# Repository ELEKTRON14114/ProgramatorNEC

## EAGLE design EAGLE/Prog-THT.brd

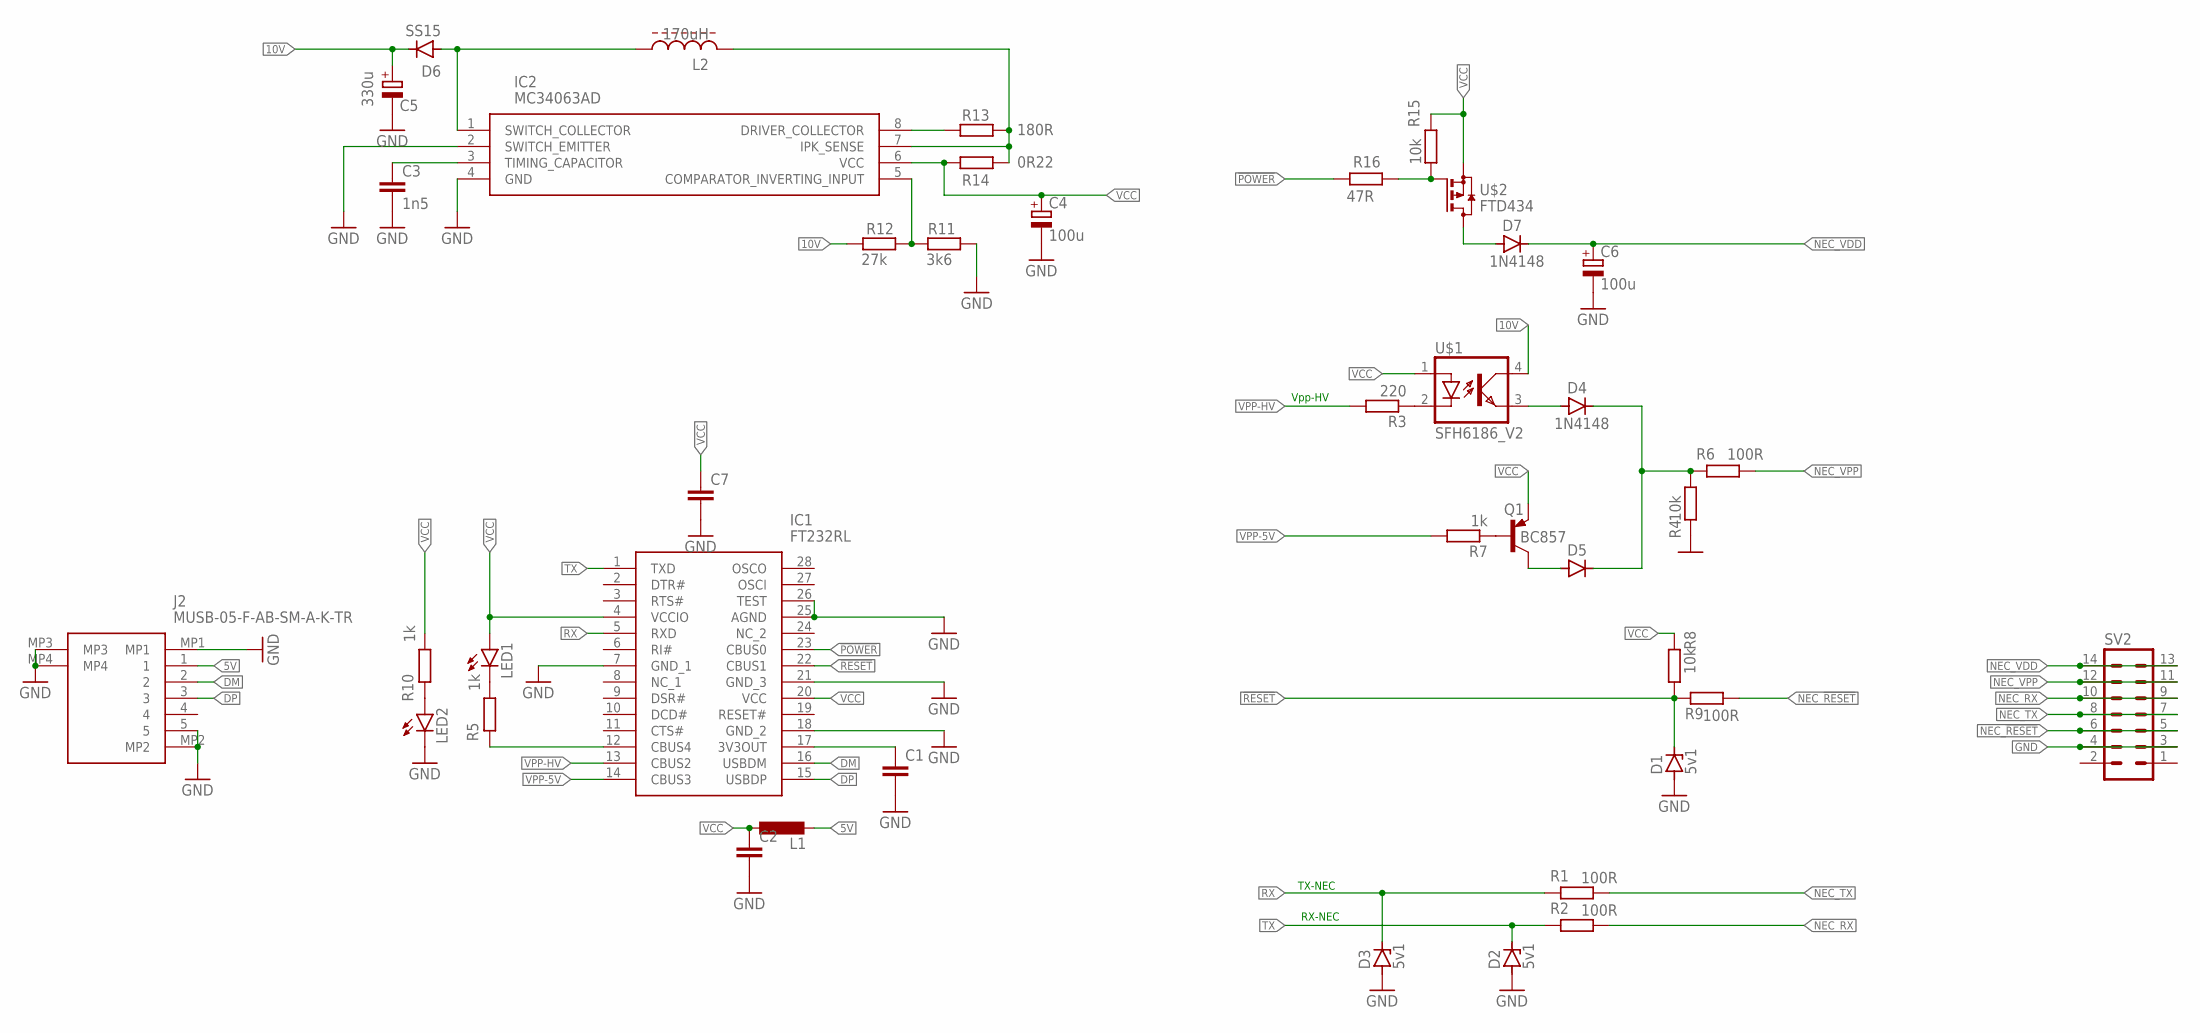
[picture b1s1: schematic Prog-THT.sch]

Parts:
C1, C2, C7: C-EUC0805; C0805
C3: 1n5; C0805
C4, C6: 100u; SMC_C
C5: 330u; SMC_C
D1, D2, D3: 5v1; DO34Z7
D4, D5, D7: 1N4148; DO35-7
D6: SS15; SMA-DO214AC
IC1: FT232RL; SOP65P778X200-28N
IC2: MC34063AD; SOIC127P600X175-8N
J2: MUSB-05-F-AB-SM-A-K-TR; MUSB05FABSMAKTR
L1: L-EUL3216C; L3216C
L2: 170uH; NN
LED1, LED2: LED3MM
Q1: BC857; SOT23-BEC
R1, R2, R6, R9: 100R; 0207/10
R3: 220; 0207/10
R4, R8: 10k; 0207/10
R5, R7, R10: 1k; 0207/10
R11: 3k6; 0207/10
R12: 27k; 0207/10
R13: 180R; 0207/10
R14: 0R22; 0207/10
R15: 10k; R0805
R16: 47R; 0207/10
SV2: MA07-2
U$1: SFH6186_V2; SOP254P978X406-4N
U$2: FTD434; SOT230P700X180-4N

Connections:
5V: J2.1, L1.2
10V: C5.+, D6.K (C), R12.2, U$1.4 (COL)
!POWER: IC1.23 (CBUS0), R16.2
!RESET: D1.C, IC1.22 (CBUS1), R8.1, R9.2
DM: IC1.16 (USBDM), J2.2
DP: IC1.15 (USBDP), J2.3
GND: C1.2, C2.2, C3.2, C4.-, C5.-, C6.-, C7.2, D1.A, D2.A, D3.A, IC1.7 (GND_1), IC1.18 (GND_2), IC1.21 (GND_3), IC1.25 (AGND), IC1.26 (TEST), IC2.2 (SWITCH_EMITTER), IC2.4 (GND), J2.5, J2.MP1, J2.MP2, J2.MP3, J2.MP4, LED2.K (C), R4.2, R11.1, SV2.3, SV2.4
unnamed: D4.C, D5.C, R4.1, R6.2
unnamed: R3.1, U$1.2 (C)
unnamed: D4.A, U$1.3 (EMIT)
unnamed: D5.A, Q1.C
unnamed: Q1.B, R7.1
unnamed: LED1.K (C), R5.1
unnamed: IC1.12 (CBUS4), R5.2
unnamed: C1.1, IC1.17 (3V3OUT)
unnamed: IC2.5 (COMPARATOR_INVERTING_INPUT), R11.2, R12.1
unnamed: IC2.8 (DRIVER_COLLECTOR), R13.1
unnamed: C3.1, IC2.3 (TIMING_CAPACITOR)
unnamed: R15.2, R16.1, U$2.1 (G)
unnamed: IC2.7 (IPK_SENSE), L2.P$2 (2), R13.2, R14.2
unnamed: D7.A, U$2.2 (D), U$2.4 (D)
unnamed: D6.A, IC2.1 (SWITCH_COLLECTOR), L2.P$1 (1)
unnamed: LED2.A, R10.2
NEC_!RESET: R9.1, SV2.5, SV2.6
NEC_RX: R2.1, SV2.9, SV2.10
NEC_TX: R1.1, SV2.7, SV2.8
NEC_VDD: C6.+, D7.C, SV2.13, SV2.14
NEC_VPP: R6.1, SV2.11, SV2.12
RX: D3.C, IC1.5 (RXD), R1.2
TX: D2.C, IC1.1 (TXD), R2.2
VCC: C2.1, C4.+, C7.1, IC1.4 (VCCIO), IC1.20 (VCC), IC2.6 (VCC), L1.1, LED1.A, Q1.E, R8.2, R10.1, R14.1, R15.1, U$1.1 (A), U$2.3 (S)
VPP-5V: IC1.14 (CBUS3), R7.2
VPP-HV: IC1.13 (CBUS2), R3.2

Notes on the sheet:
TX-NEC
RX-NEC
Vpp-HV

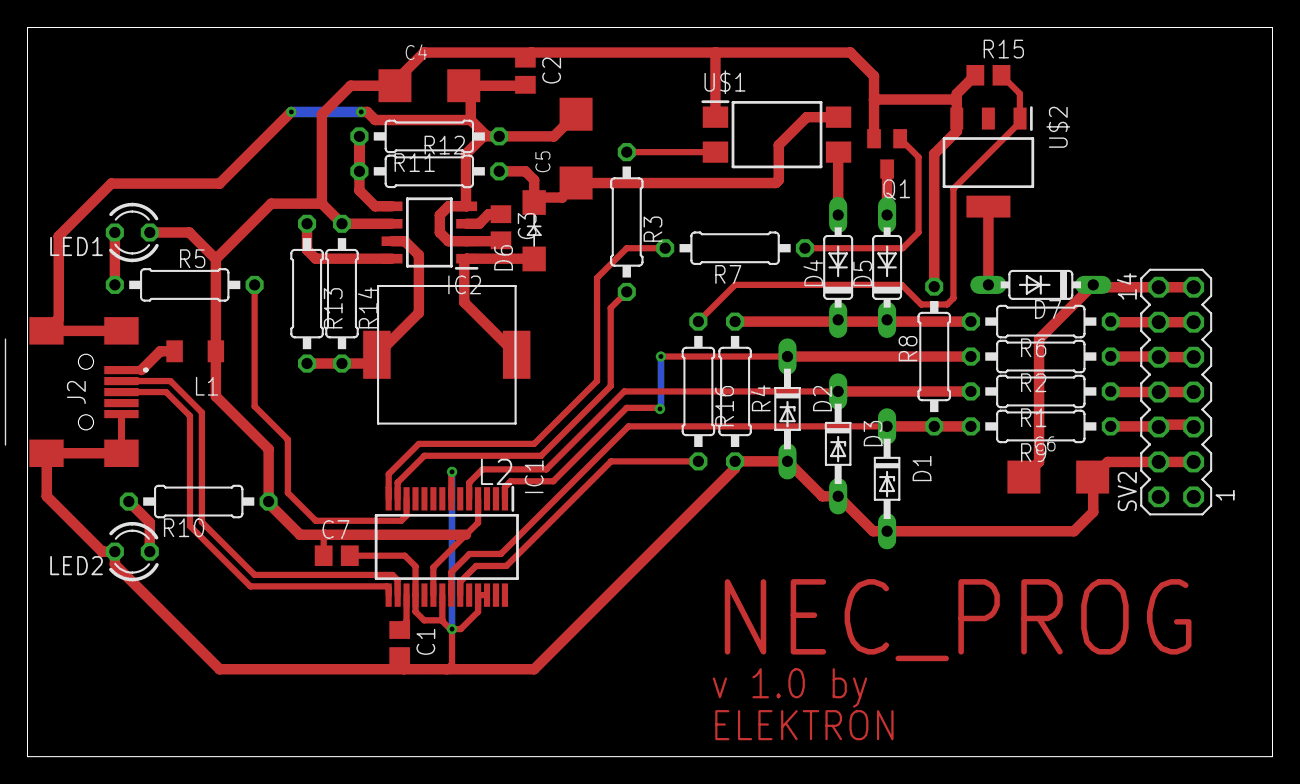
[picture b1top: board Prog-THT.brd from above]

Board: 2 copper layers, 90.5 x 53.0 mm, 41 parts (0 on the bottom side), 33 nets.

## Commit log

2024-10-03 Dodaj pliki .gitignore i .gitattributes.
2024-10-03 Dodaj pliki projektów.
2024-10-03 /uzupełnienie plików dodatkowych
2024-10-03 Create LICENSE
2024-10-05 Poprawiono niektóre usterki, dodano nowe funkcje i błędy
2024-11-04 Kosmetyka
2024-11-13 Fix binary table & Add Hex Support & Add NuGet FTDI
